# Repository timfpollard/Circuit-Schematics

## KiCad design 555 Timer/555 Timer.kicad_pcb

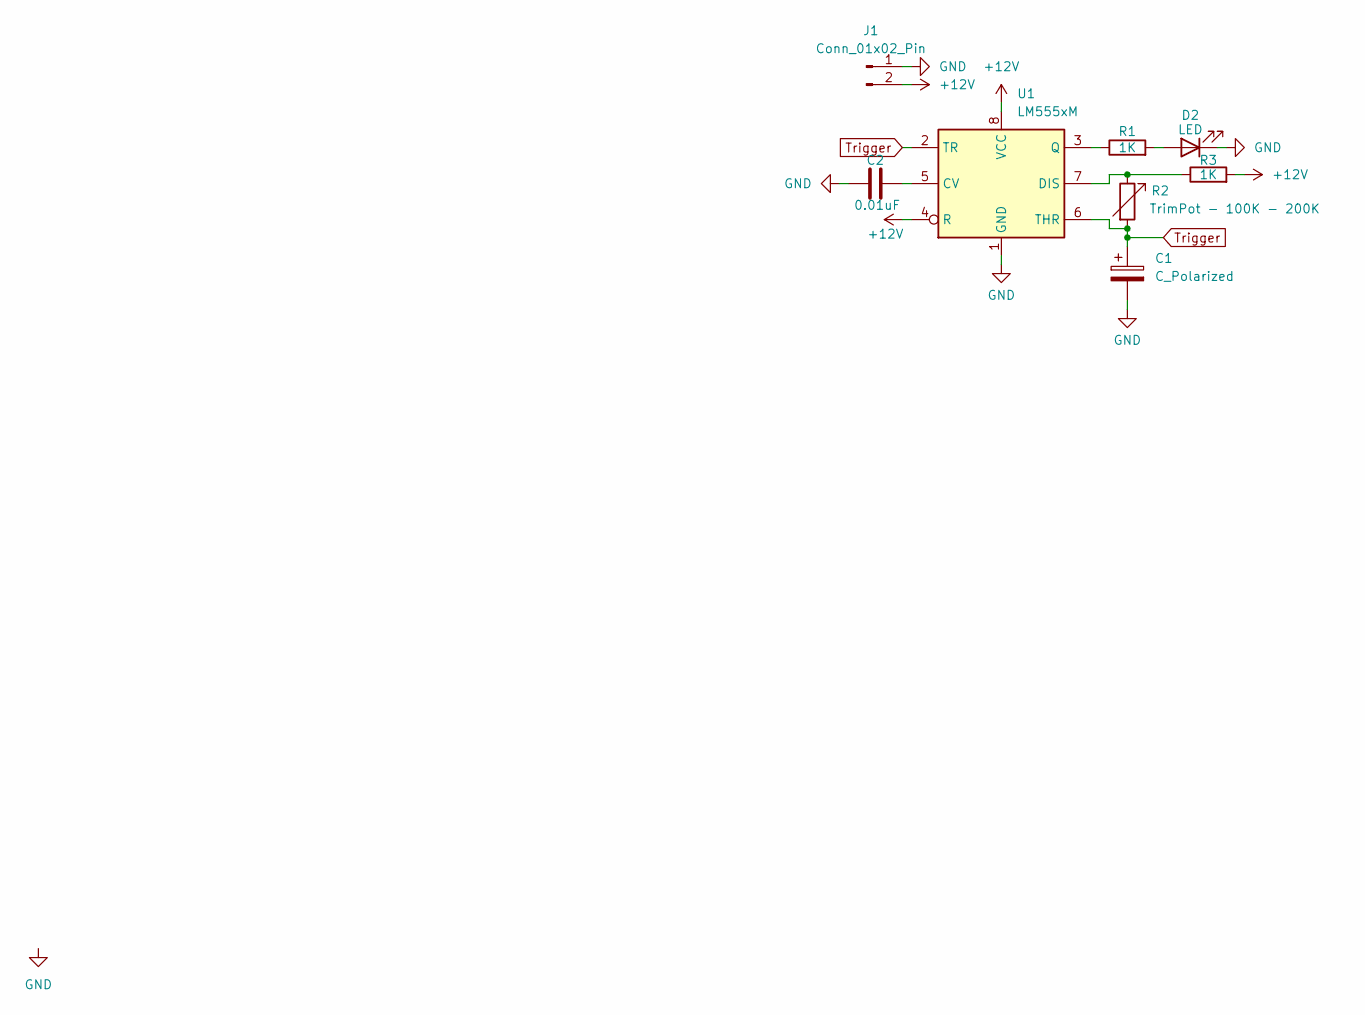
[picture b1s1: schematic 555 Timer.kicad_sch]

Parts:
C1: C_Polarized; CP_Radial_D5.0mm_P2.00mm
C2: 0.01uF; C_Disc_D5.0mm_W2.5mm_P5.00mm
D2: LED; LED_D5.0mm
J1: Conn_01x02_Pin; PinSocket_1x02_P2.54mm_Vertical
R1, R3: 1K; R_0603_1608Metric_Pad0.98x0.95mm_HandSolder
R2: TrimPot - 100K - 200K; Potentiometer_Bourns_3266P_Horizontal
U1: LM555xM; SOIC-8_3.9x4.9mm_P1.27mm

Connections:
+12V: J1.2, R3.2, U1.4 (R), U1.8 (VCC)
GND: C1.2, C2.1, D2.1 (K), J1.1, U1.1 (GND)
unnamed: D2.2 (A), R1.2
unnamed: C2.2, U1.5 (CV)
unnamed: R2.1, R3.1, U1.7 (DIS)
unnamed: R1.1, U1.3 (Q)
Trigger: C1.1, R2.2, U1.2 (TR), U1.6 (THR)

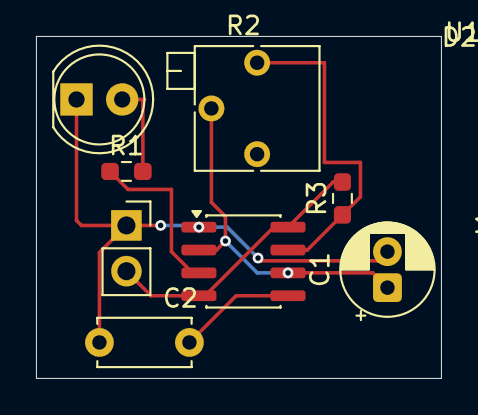
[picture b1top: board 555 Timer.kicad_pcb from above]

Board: 2 copper layers, 22.5 x 19.0 mm, 8 parts (0 on the bottom side), 7 nets.

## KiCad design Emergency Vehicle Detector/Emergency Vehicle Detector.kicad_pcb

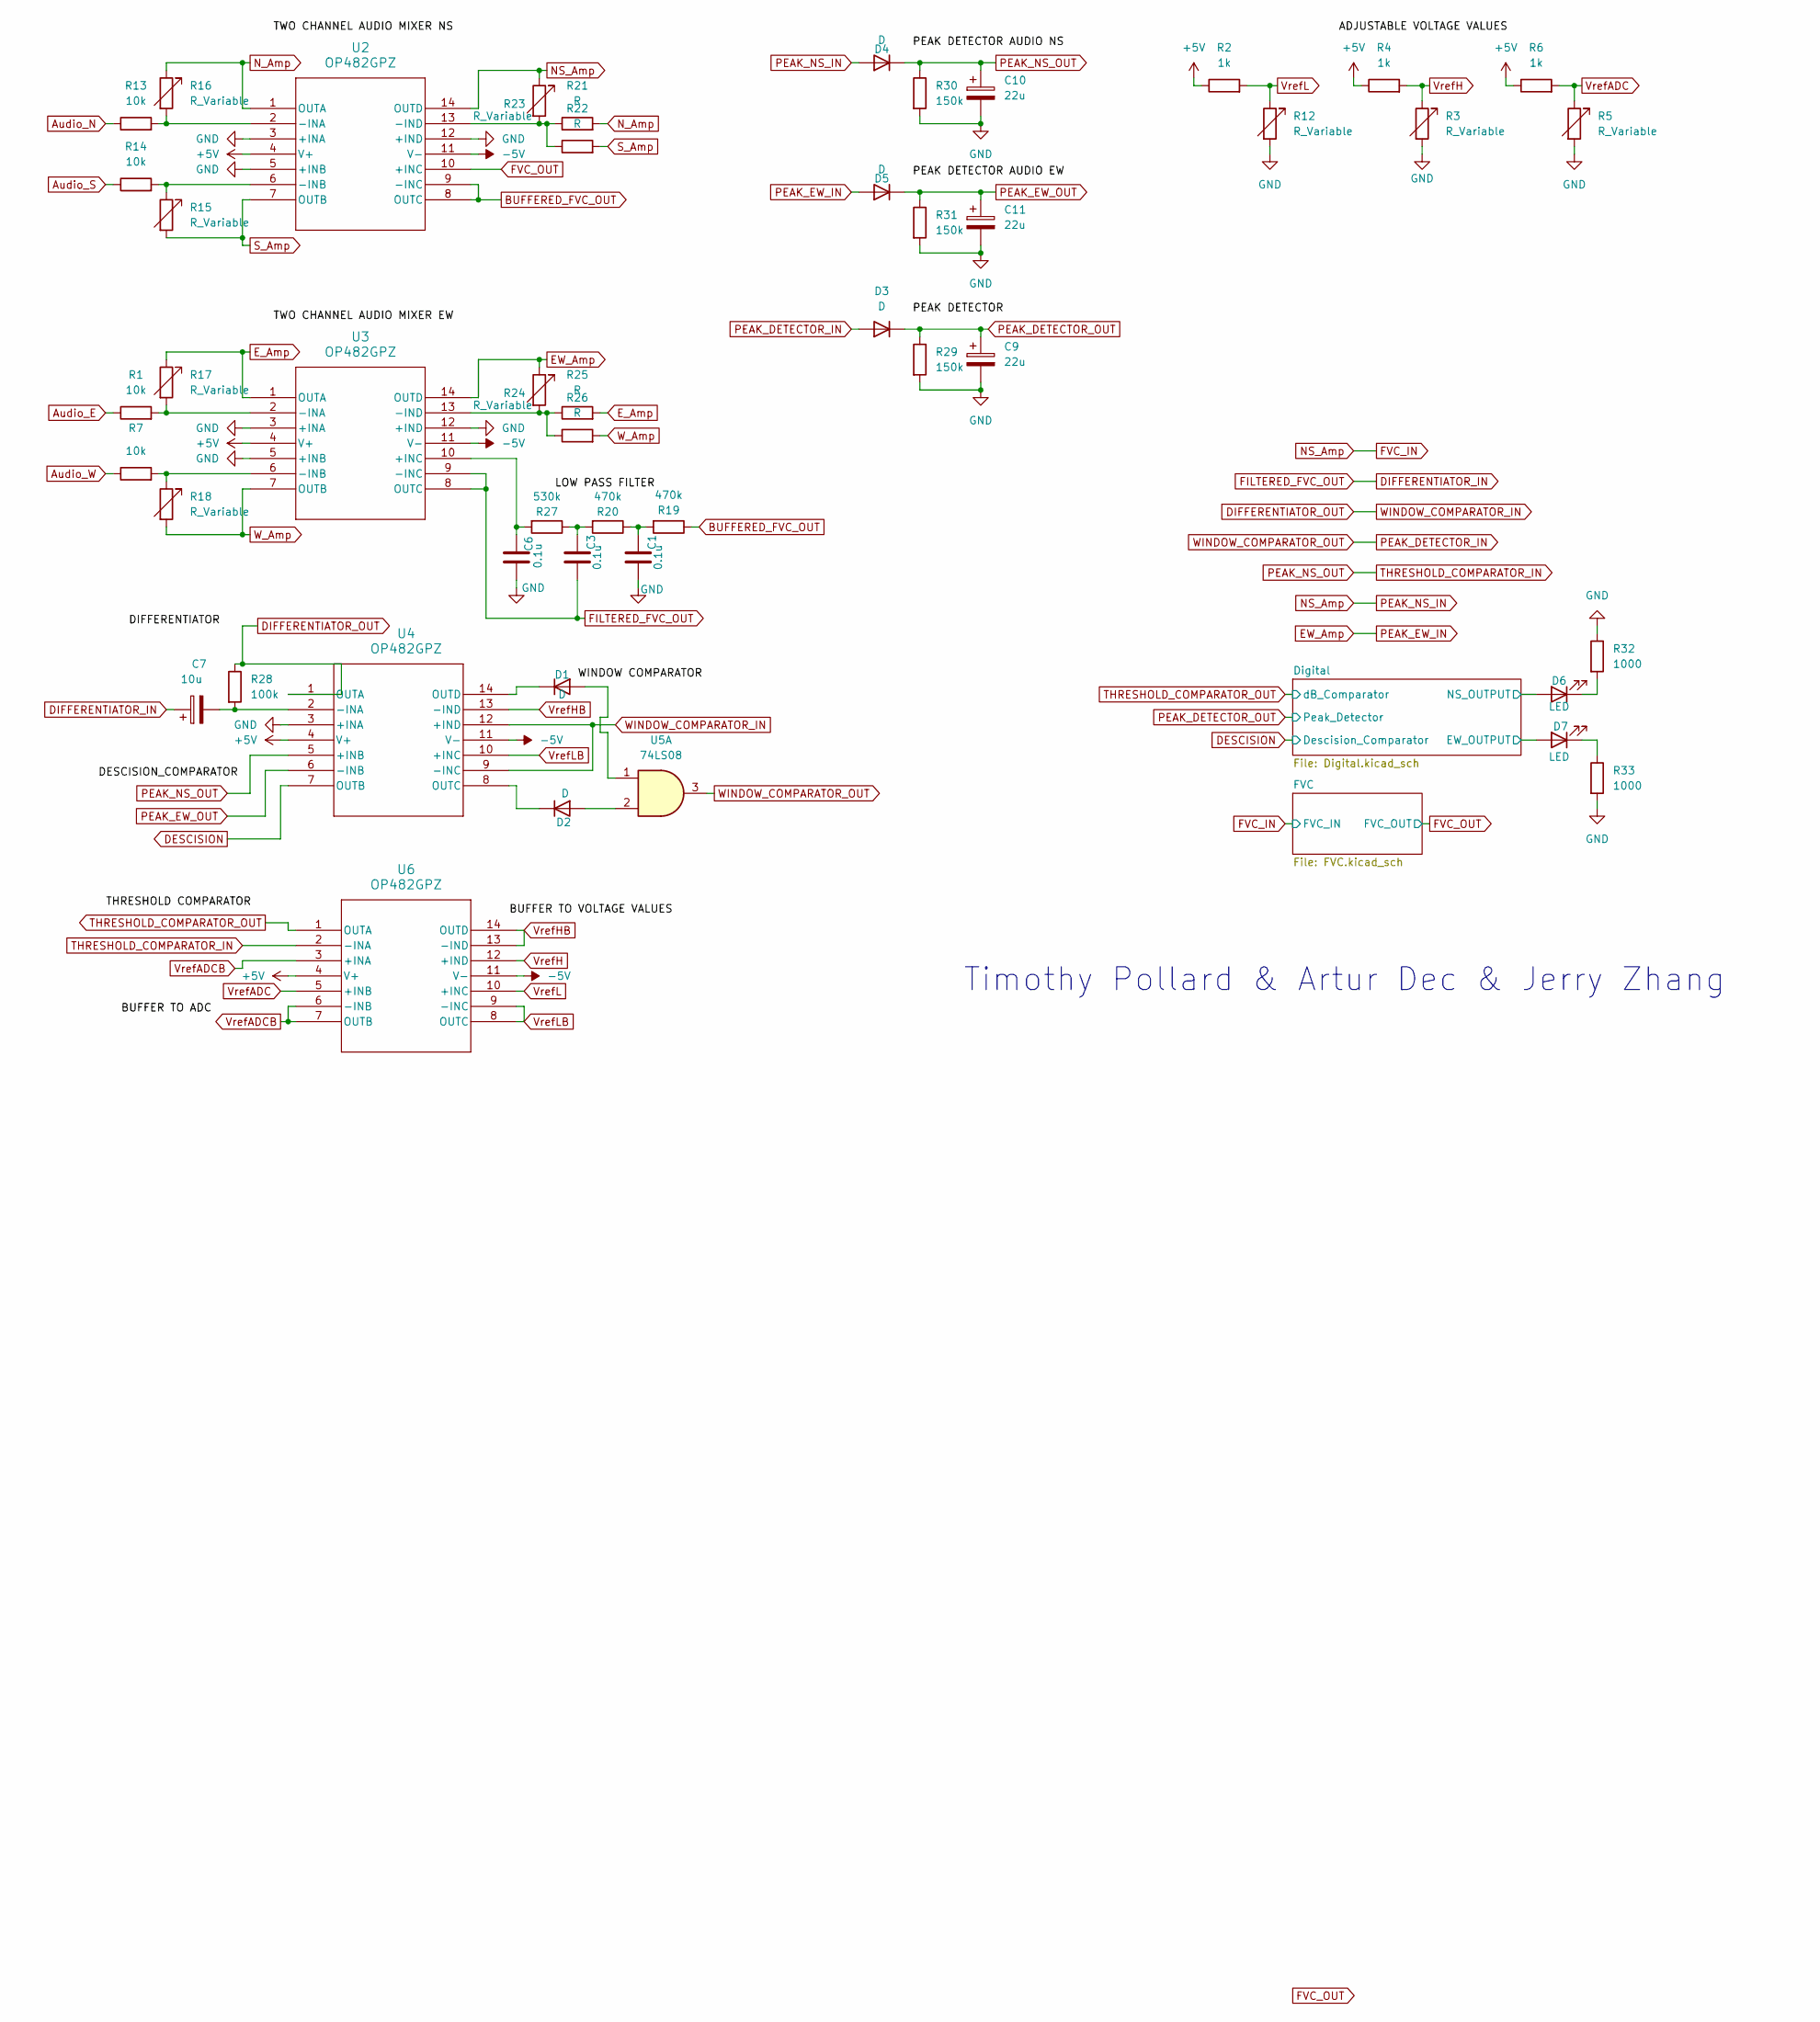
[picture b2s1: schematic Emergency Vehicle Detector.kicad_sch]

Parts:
C1, C3, C6: 0.1u; C_Disc_D5.0mm_W2.5mm_P5.00mm
C7: 10u; C_Disc_D5.0mm_W2.5mm_P5.00mm
C9, C10, C11: 22u; C_Radial_D5.0mm_H7.0mm_P2.00mm
D1, D2, D3, D4, D5: D; D_A-405_P7.62mm_Horizontal
D6, D7: LED
R1, R7, R13, R14: 10k; R_Axial_DIN0309_L9.0mm_D3.2mm_P12.70mm_Horizontal
R2, R4, R6: 1k; R_Axial_DIN0309_L9.0mm_D3.2mm_P12.70mm_Horizontal
R3, R5, R12, R15, R16, R17, R18, R23, R24: R_Variable; Potentiometer_Bourns_3386P_Vertical
R19, R20: 470k; R_Axial_DIN0309_L9.0mm_D3.2mm_P12.70mm_Horizontal
R21, R22, R25, R26: R; R_Axial_DIN0309_L9.0mm_D3.2mm_P12.70mm_Horizontal
R27: 530k; R_Axial_DIN0309_L9.0mm_D3.2mm_P12.70mm_Horizontal
R28: 100k; R_Axial_DIN0309_L9.0mm_D3.2mm_P12.70mm_Horizontal
R29, R30, R31: 150k; R_Axial_DIN0309_L9.0mm_D3.2mm_P12.70mm_Horizontal
R32, R33: 1000
U2, U3, U4, U6: OP482GPZ; N_14_ADI
U5: 74LS08; N14

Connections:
+5V: R2.1, R4.1, R6.1, U2.4 (V+), U3.4 (V+), U4.4 (V+), U6.4 (V+); also elsewhere on the board
-5V: U2.11 (V-), U3.11 (V-), U4.11 (V-), U6.11 (V-)
/Digital/EW_OUTPUT: D7.2 (A); also elsewhere on the board
/Digital/NS_OUTPUT: D6.2 (A); also elsewhere on the board
Audio_E: R1.1
Audio_N: R13.1
Audio_S: R14.1
Audio_W: R7.1
BUFFERED_FVC_OUT: R19.1, U2.8 (OUTC), U2.9 (-INC)
DESCISION: U4.7 (OUTB); also elsewhere on the board
DIFFERENTIATOR_IN: C3.1, C7.1, U3.8 (OUTC), U3.9 (-INC)
DIFFERENTIATOR_OUT: R28.1, U4.1 (OUTA), U4.9 (-INC), U4.12 (+IND)
EW_Amp: D5.2 (A), R24.1, U3.14 (OUTD)
E_Amp: R17.1, R25.2, U3.1 (OUTA)
FVC_IN: D4.2 (A), R23.1, U2.14 (OUTD); also elsewhere on the board
FVC_OUT: U2.10 (+INC); also elsewhere on the board
GND: C1.1, C6.2, C9.2, C10.2, C11.2, R3.2, R5.2, R12.2, R29.2, R30.2, R31.2, R32.1, R33.2, U2.3 (+INA), U2.5 (+INB), U2.12 (+IND), U3.3 (+INA), U3.5 (+INB), U3.12 (+IND), U4.3 (+INA); also elsewhere on the board
N_Amp: R16.1, R21.2, U2.1 (OUTA)
unnamed: C1.2, R19.2, R20.1
unnamed: C3.2, R20.2, R27.1
unnamed: D1.2 (A), U5.1
unnamed: D1.1 (K), U4.14 (OUTD)
unnamed: D2.2 (A), U5.2
unnamed: D2.1 (K), U4.8 (OUTC)
unnamed: D6.1 (K), R32.2
unnamed: D7.1 (K), R33.1
unnamed: R13.2, R16.2, U2.2 (-INA)
unnamed: R14.2, R15.1, U2.6 (-INB)
unnamed: R21.1, R22.1, R23.2, U2.13 (-IND)
unnamed: C6.1, R27.2, U3.10 (+INC)
unnamed: R1.2, R17.2, U3.2 (-INA)
unnamed: R7.2, R18.1, U3.6 (-INB)
unnamed: R24.2, R25.1, R26.1, U3.13 (-IND)
unnamed: C7.2, R28.2, U4.2 (-INA)
PEAK_DETECTOR_IN: D3.2 (A), U5.3
PEAK_DETECTOR_OUT: C9.1, D3.1 (K), R29.1; also elsewhere on the board
PEAK_EW_OUT: C11.1, D5.1 (K), R31.1, U4.6 (-INB)
PEAK_NS_OUT: C10.1, D4.1 (K), R30.1, U4.5 (+INB), U6.2 (-INA)
S_Amp: R15.2, R22.2, U2.7 (OUTB)
THRESHOLD_COMPARATOR_OUT: U6.1 (OUTA); also elsewhere on the board
VrefADC: R5.1, R6.2, U6.5 (+INB)
VrefADCB: U6.3 (+INA), U6.6 (-INB), U6.7 (OUTB)
VrefH: R3.1, R4.2, U6.12 (+IND)
VrefHB: U4.13 (-IND), U6.13 (-IND), U6.14 (OUTD)
VrefL: R2.2, R12.1, U6.10 (+INC)
VrefLB: U4.10 (+INC), U6.8 (OUTC), U6.9 (-INC)
W_Amp: R18.2, R26.2, U3.7 (OUTB)

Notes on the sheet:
Timothy Pollard & Artur Dec & Jerry Zhang

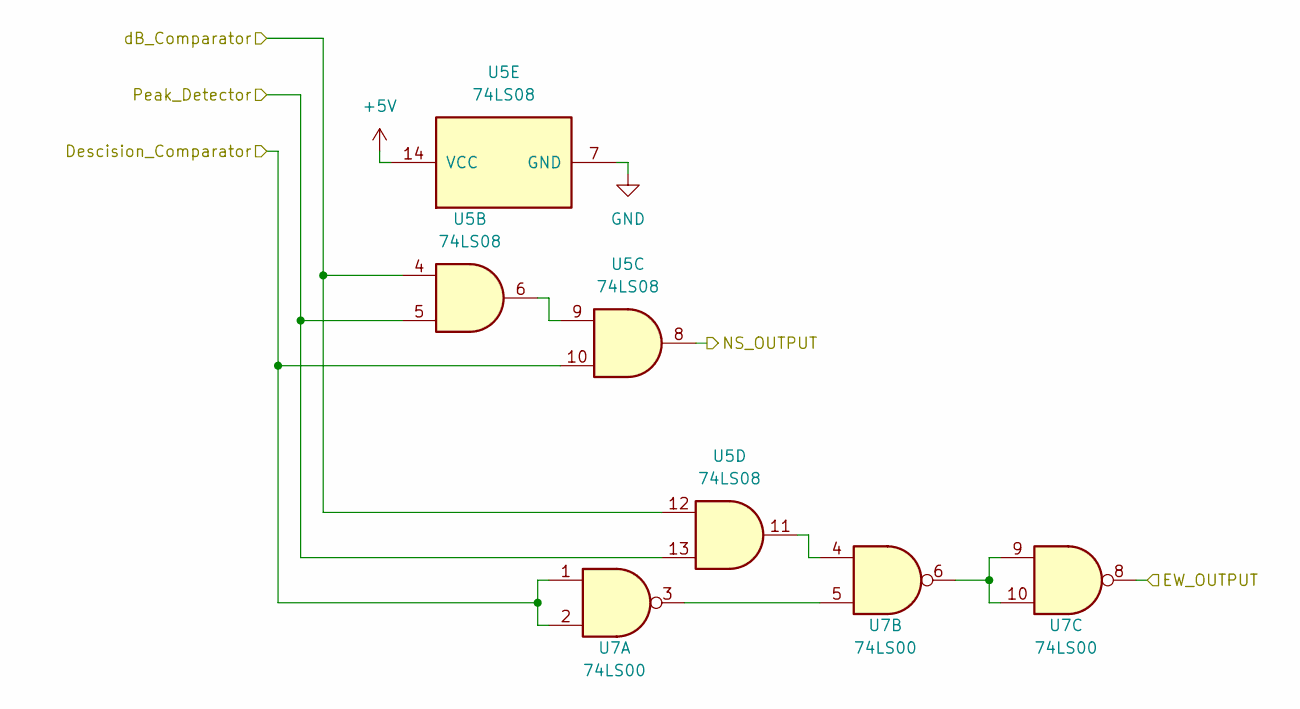
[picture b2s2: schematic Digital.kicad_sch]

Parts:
U5: 74LS08; N14
U7: 74LS00; N14

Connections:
+5V: U5.14 (VCC); also elsewhere on the board
/Digital/EW_OUTPUT: U7.8; also elsewhere on the board
/Digital/NS_OUTPUT: U5.8; also elsewhere on the board
DESCISION: U5.10, U7.1, U7.2; also elsewhere on the board
GND: U5.7 (GND); also elsewhere on the board
unnamed: U5.6, U5.9
unnamed: U5.11, U7.4
unnamed: U7.3, U7.5
unnamed: U7.6, U7.9, U7.10
PEAK_DETECTOR_OUT: U5.5, U5.13; also elsewhere on the board
THRESHOLD_COMPARATOR_OUT: U5.4, U5.12; also elsewhere on the board

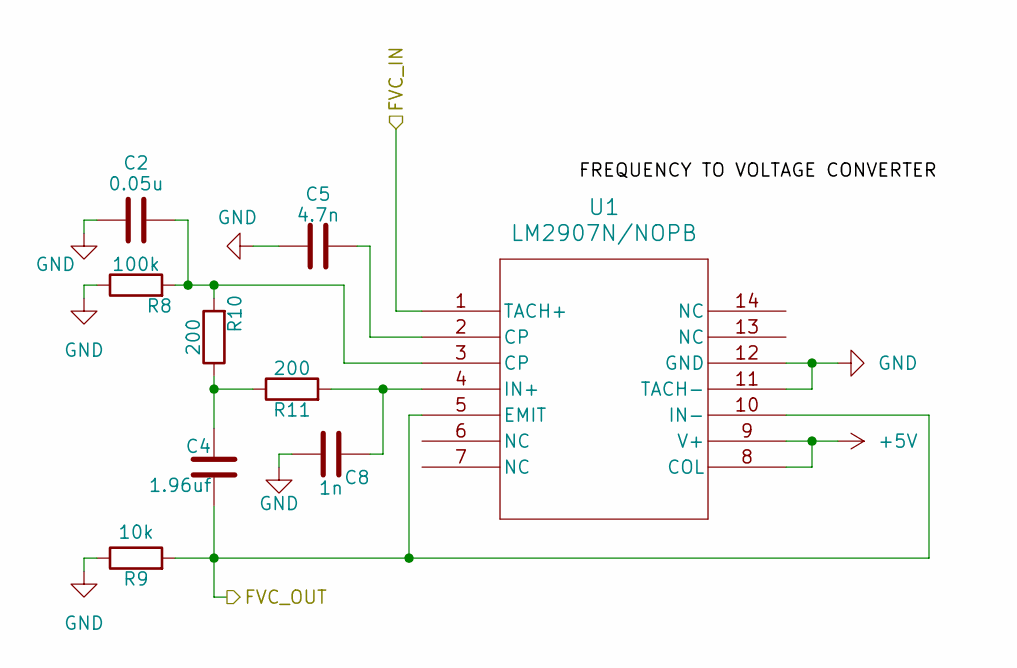
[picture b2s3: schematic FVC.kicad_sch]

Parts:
C2: 0.05u; C_Disc_D5.0mm_W2.5mm_P5.00mm
C4: 1.96uf; C_Disc_D5.0mm_W2.5mm_P5.00mm
C5: 4.7n; C_Disc_D5.0mm_W2.5mm_P5.00mm
C8: 1n; C_Disc_D5.0mm_W2.5mm_P5.00mm
R8: 100k; R_Axial_DIN0309_L9.0mm_D3.2mm_P12.70mm_Horizontal
R9: 10k; R_Axial_DIN0309_L9.0mm_D3.2mm_P12.70mm_Horizontal
R10, R11: 200; R_Axial_DIN0309_L9.0mm_D3.2mm_P12.70mm_Horizontal
U1: LM2907N/NOPB; N14A_TEX

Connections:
+5V: U1.8 (COL), U1.9 (V+); also elsewhere on the board
FVC_IN: U1.1 (TACH+); also elsewhere on the board
FVC_OUT: C4.1, R9.2, U1.5 (EMIT), U1.10 (IN-); also elsewhere on the board
GND: C2.1, C5.1, C8.1, R8.1, R9.1, U1.11 (TACH-), U1.12 (GND); also elsewhere on the board
unnamed: C2.2, R8.2, R10.2, U1.3 (CP)
unnamed: C4.2, R10.1, R11.1
unnamed: C5.2, U1.2 (CP)
unnamed: C8.2, R11.2, U1.4 (IN+)

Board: 2 copper layers, 58 parts (0 on the bottom side), 51 nets, no tracks yet.

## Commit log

2026-06-28 Add Emergency Vehicle Detector file
